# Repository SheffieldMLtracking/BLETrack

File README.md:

Code for Bluetooth Low Energy bee tracking system.

+ "Transmitter" folder contains the code to be flashed to the BT832X/BM832E transmitter board.
+ "Receiver" folder contains the code to be flashed to the DA14531 chip on-tag and the 'Active Scanner' code for testing & diagnostics.
+ "To Print" folder contains [FreeCAD](https://www.freecad.org/) files of the transmitter housing.
+ "Path Inference" folder contains code to process data from tag/dev board
+ Test data stored [here](https://github.com/SheffieldMLtracking/bluetooth_experiments)

## Notes on Programming Transmitter
### Transmitter programming:
+ Requires [nRF Connect SDK](https://www.nordicsemi.com/Products/Development-software/nRF-Connect-SDK).
+ Create a build for the nrf52dk_nrf52832 and add the included device tree overlay.
+ Connect nrf52dk and BT832X/BM832E to the computer via JLINK (done via micro USB cable). Connect DEBUG OUT on nrf52dk to DEBUG IN on BT832X/BM832E:
+ flashthisfirst.c must be flashed to the BT832X/BM832E first - then main.c can be flashed.

NOTE: P0.31 is used for encoder output A, P0.30 for encoder output B and P0.11 for hall effect sensor input.

### Receiver programming:
+ Requires Keil uVision and configuration of environment as shown [here](https://lpccs-docs.renesas.com/UM-B-117-DA14531-Getting-Started-With-The-Pro-Development-Kit/01_abstract/abstract.html).
+ To program a receiver tag via flashing code to the OTP memory, follow [these](https://lpccs-docs.renesas.com/Tutorial_SDK6/otp_prog.html) instructions. **If you need to debug code on a tag, do not flash to the OTP.** DA14531 USB Development Kit can be used as a serial wire debug probe to debug code on an external DA14531 chip on the receiver tag using [this](https://lpccs-docs.renesas.com/Tutorial_SDK6/debug_probe.html) configuration of SWIO cables and DIP switches.
+ Note: binary for compiled DA14531 is found in Keil/DA14531_OUT/Objects.
+ Note: USB dev kit switches should be configured as shown: 

## Usage of the System
### Setting Up Transmitters
+ Charge transmitters before field trial!
+ Each transmitter is placed onto a tripod across the landscape. The 0 degree point on the tripod (denoted by the small magnet on the base the transmitter sits in) should be pointed north using a compass before placing the transmitter itself upon the tripod. The transmitter should be level with the ground and mounted as high up as possible.
+ As each transmitter is turned on, the time between turning each on should be taken using a stop watch. This time is later used to zero the time readouts in the packets.
+ Using the "Active Scanner" code downloaded to the DA14531 USB Dev Kit, the serial output from the dev kit - which can be accessed using a serial terminal program such as Tera Term - should be used to verify the functionality of the tramsitters. The packets recieved by the active scanner are in the following form and should be assessed to ensure that the transmitter is in fact transmitting and that the motor is reading out ~360 degrees of rotation, resetting at the zero point. If there is an issue, the transmitter may need reprogramming, regarching or the motor encoder may have been knocked out of place.

+ Each transmitter currently has a range of approximately 100m (further at peak signal strength but not currently used in angle inference algorithm). The area tracked should be covered by at least 2, preferably 3 transmitters.

### Using a Receiever Tag
+ A programmed tag should be allowed to drain fully to hardware reset, then be charged and attatched to a bee.
+ Following retrieval, put the tag on charge and apply ground to the interrupt pin to switch the tag into transmit mode.
+ The data of each packet is encoded in the destination addr, in the same form as the transmitted packets except the RSSI of the packet is encoded in the leftmost byte. Using a bluetooth sniffer (reccomended [nrf52 BLE sniffer](https://www.nordicsemi.com/Products/Development-tools/nRF-Sniffer-for-Bluetooth-LE)) and Wireshark the transmitted packets can be read. The following filter shows only read packets:
<p align=center>btle.advertising_header.pdu_type == 0x01 && !_ws.expert && btle.advertising_address == 80:ea:ca:70:00:04</p>

### Performing Infernece
+ Instructions for performing path inference on data are located in PathInferenceFinalCut.inpyb

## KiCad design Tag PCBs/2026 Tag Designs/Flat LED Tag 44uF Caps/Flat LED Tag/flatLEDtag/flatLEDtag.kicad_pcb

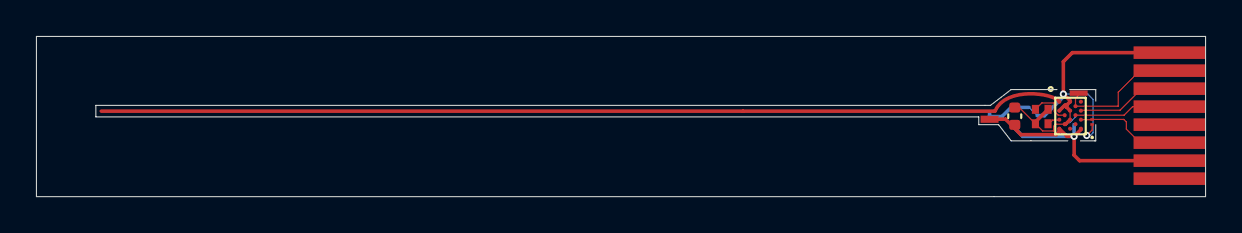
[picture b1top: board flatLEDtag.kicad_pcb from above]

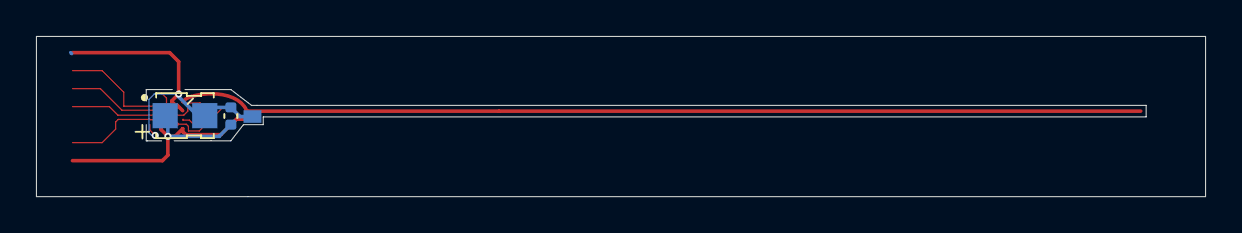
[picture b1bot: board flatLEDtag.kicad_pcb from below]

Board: 2 copper layers, 64.9 x 8.9 mm, 8 parts (2 on the bottom side), 9 nets.

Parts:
AE1: Antenna
C1, C3: C; C_0402_1005Metric
C2: CPH3225A; CAPCP3225X100N_improved
D1: LED; KPG-0402SURKKC-TT
J1: Conn_01x08; FPC_1x08_P1.00mm_plug_3mm
U1: DA14531_17-ball_WLCSP
Y1: Crystal_GND24; Crystal_SMD_Abracon_ABM13W-4Pin_1.2x1.0mm

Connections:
/+VE: C1.1, C2.1, C3.1, J1.7, U1.G1 (VBAT_LOW), U1.G5 (VBAT_HIGH)
/GND: C1.2, C2.2, C3.2, D1.1 (K), J1.1, U1.A3 (RFIOm), U1.C1 (GND_RF2), U1.C3 (GND_RF1), U1.E3 (VSS), U1.F2 (GND_DCDC), Y1.2, Y1.4
/IR: J1.2, U1.B4 (P0_3/XTAL32kp)
/LED +VE: D1.2 (A), J1.6, U1.E5 (P0_1/ADC0/SWDIO)
unnamed: J1.3, U1.C5 (P0_2/ADC1/SWCLK)
unnamed: J1.4, U1.D4 (P0_5/SWDIO)
unnamed: J1.5, U1.F4 (P0_0/RST)
unnamed: U1.E1 (XTAL32Mm), Y1.3
unnamed: U1.D2 (XTAL32Mp), Y1.1

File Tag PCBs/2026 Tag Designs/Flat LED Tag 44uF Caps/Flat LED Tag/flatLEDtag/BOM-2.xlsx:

|  |  | xxxx xxxx xxxxx xxPCS BOM (Sample Bill of Materials)
Item # | *Designator | *Qty | Manufacturer | *Mfg Part # | Description / Value | *Package/Footprint | Type | Your Instructions / Notes
1 | C1 | 1 | KYOCERA AVX | CM05X5R226M04AH | Multilayer Ceramic Capacitors SMD, 22 µF, 4V. [note if different cap is used: n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 | 0402 [1005 Metric] | SMD
2 | C3 | 1 | KYOCERA AVX | CM05X5R226M04AH | Multilayer Ceramic Capacitors SMD, 22 µF, 4V. [note if different cap is used: n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 | 0402 [1005 Metric] | SMD
3 | U1 | 1 | Renesas / Dialog | DA14531-00000OG2 | Bluetooth Low Energy 5.1 SoC with integrated ARM Cortex M0+ | WLCSP-17 | SMD | Pin A1 indicated with silkscreen circle (at top left, close to part Y1)
3 | Y1 | 1 | Seiko Semiconductors | ABM13W-32.0000MHZ-5-DH7G-T5 | 32.0000MHz Quartz Crystal. 5pF load cap. 7ppm freq tol. 15ppm freq stab. [requi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 | SMD (4 pins) | SMD | Pin 1 indicated by silkscreen dot (nearest IC). Note that it is pin 2 that has 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
4 | C2 | 1 | Seiko Semiconductors | CPH3225A | Supercapacitor: electric double layer capacitor. 3.3V, 11mF, (internal impedanc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 | SMD (2 pins), 3.2mm x 2.5mm | SMD | Positive pin indicated with silkscreen + and dot. Also shape of capacitor has n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
5 | D1 | 1 | Kingbright | KPG-0402SURKKC-TT | 0.45 mm x 0.25 mm SMD Hyper red LED, 0.2 mm thickness. AlGaInP on GaAs substrat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 | 0402 [1005 Metric] | SMD | LED is placed in reverse bias, pin 1 goes to GND and pin 2 goes to a pin of par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
Need a quick and accurante quote? Need an efficient production? Please read SMT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
Click for Instructions on How to Create a BOM

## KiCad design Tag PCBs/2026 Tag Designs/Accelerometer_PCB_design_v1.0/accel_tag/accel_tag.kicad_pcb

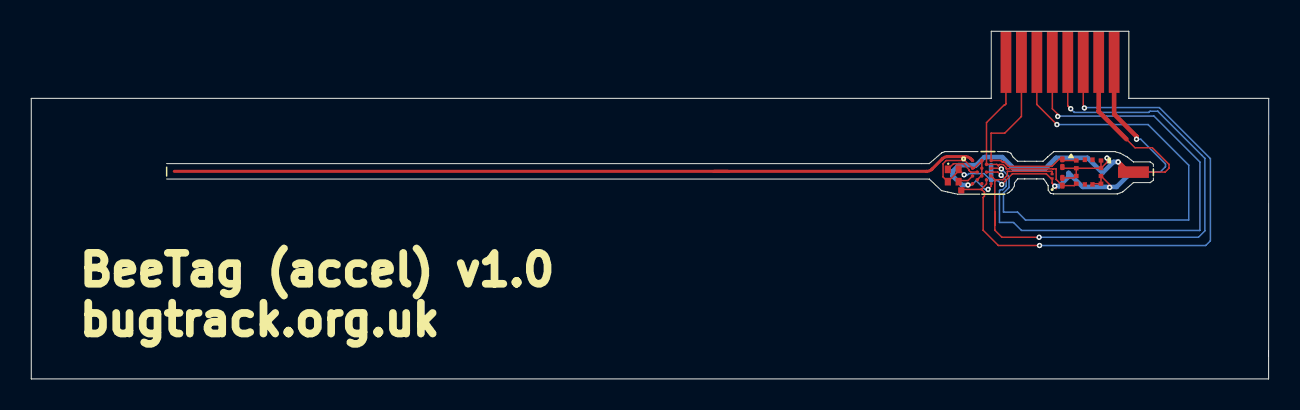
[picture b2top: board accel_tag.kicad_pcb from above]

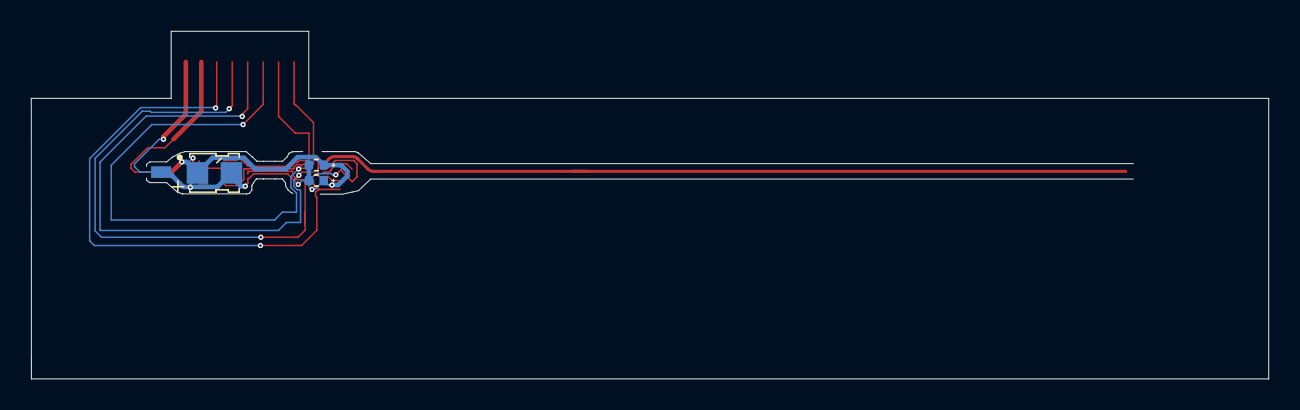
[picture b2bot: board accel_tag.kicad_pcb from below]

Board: 2 copper layers, 80.1 x 22.5 mm, 14 parts (4 on the bottom side), 10 nets.

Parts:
AE1: Antenna
C1: CPH3225A; CAPCP3225X100N_improved
C2, C3: C_Polarized; C_0402_1005Metric
CHARGING_GND1: Charging ground pin; Charging_pad_0.75x2mm
CHARGING_POSITIVE1: Charging positive pin; Charging_pad_0.75x2mm
D1: LED; KPG-0402SURKKC-TT
J1: Conn_01x08; FPC_1x08_P1.00mm_plug_3mm
R1, R2: 10K; R_01005_0402Metric
TP1: TestPoint; TestPoint_Pad_1.0x1.0mm
U1: LIS2DU12TR; LGA-12L_LIS2DU12_STM
U2: DA14531-00000OG2; DA14531_17-ball_WLCSP
Y1: ABM13W-32MHz; Crystal_SMD_Abracon_ABM13W-4Pin_1.2x1.0mm

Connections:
GNDREF: C1.2, C2.2, C3.2, CHARGING_GND1.1, D1.1 (K), J1.8, U1.6 (GND), U1.7 (RES), U1.8 (GND), U2.A3 (RFIOM), U2.C1 (GND_RF2), U2.C3 (GND_RF1), U2.E3 (VSS), U2.F2 (GND_DCDC), Y1.2 (GND), Y1.4 (NC)
unnamed: D1.2 (A), J1.5, U2.E5 (P0_1/ADC0/SWDIO)
unnamed: J1.1, R2.2, U1.4 (SDA/SDI/SDO), U2.B4 (P0_3/XTAL32KP)
unnamed: J1.2, R1.2, U1.1 (SCL/SPC), U2.A5 (P0_4/XTAL32KM)
unnamed: J1.3, U2.C5 (P0_2/ADC1/SWCLK)
unnamed: J1.4, U2.D4 (P0_5/SWDIO)
unnamed: J1.6, TP1.1, U2.F4 (RST/P0_0)
unnamed: C1.1, C2.1, C3.1, CHARGING_POSITIVE1.1, J1.7, R1.1, R2.1, U1.2 (CS), U1.3 (SDO/SA0), U1.9 (VDD), U1.10 (VDD_IO), U2.G1 (VBAT_LOW), U2.G5 (VBAT_HIGH)
unnamed: U2.E1 (XTAL32MM), Y1.3
unnamed: U2.D2 (XTAL32MP), Y1.1

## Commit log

2024-03-18 Update README.md
    Updated with information on file structure and operating procedures
2024-03-18 Update README.md
    Added build settings instructions for transmitter code.
2024-03-18 add transmitter files
2024-03-18 added transmission of time
2024-03-19 Added receiver code
2024-03-19 Update da1458x_config_basic.h
    defined CFG_POWER_MODE_BYPASS
2024-03-21 added rtc and cessation of scanning support
2024-03-21 Clean up of test code
2024-03-26 Added Hall Effect IR
    Resets angle of encoder readout when HE is triggered, uses pin 11 and SW0 gpio-ir
2024-03-26 Fixed Commented Configs
    CONFIG_BT_ID_MAX and CONFIG_SENSOR were re-enabled
2024-03-26 nrf52dk programming example img
2024-03-26 nrf52dk debug example
2024-03-27 Update README.md
    Receiver programming instructions
2024-03-27 Yagi Mount File
2024-03-27 Alleviated Motor Drift
    Angle readout stored and processed as float - rounding was a source of drift. Also updated angle conversion to use 488.3:1 ratio as reported by the 488:1 Metal Gearmotor 20Dx46L mm 12V CB with Extend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
2024-03-27 Set Transmission Power to 3dBm
    CONFIG_BT_CTLR_TX_PWR_ANTENNA added and set
2024-03-27 Added rest of FCStd files
2024-04-02 Motor Drift Fix w/o Floating Points
2024-04-03 size adjustments
2024-04-03 tripod mount and HE sensor partial completion
2024-04-04 First draft of increased data storage and expression
2024-04-04 improved bearing and motor fit
2024-04-04 HE Sensor Mount v1
2024-04-11 Added WS Filter
2024-04-15 Added qdec toolchain instructions in-line
2024-04-15 terminology
2024-04-16 Added support for longer mount
2024-05-22 Added HE threshold, fixed transmission lag
2024-05-22 Fixed HE pin
2024-05-22 Improved HE sensor through hole
2024-06-26 Fixed HE and tripod mount issues
2024-11-12 PCB old version
2025-06-13 Initial (untested) version of the marking pot
2025-09-24 Upload LED tags
2026-03-19 fix path that doesn't work in windows
2026-03-19 remove broken path name
2026-04-16 branch init for magic packet code
2026-04-16 transmits 'magic packet' - probably needs to be more unique
2026-04-16 transmit addr now retrograde of Rx addr
2026-04-16 changed addr as MSB was messing with some SDK rules?
2026-04-27 Rename city active_scanner.zip to city_active_scanner.zip
2026-05-27 new tag designs
2026-05-27 Removed more debug to make transmission faster
2026-05-27 2026 tag code
